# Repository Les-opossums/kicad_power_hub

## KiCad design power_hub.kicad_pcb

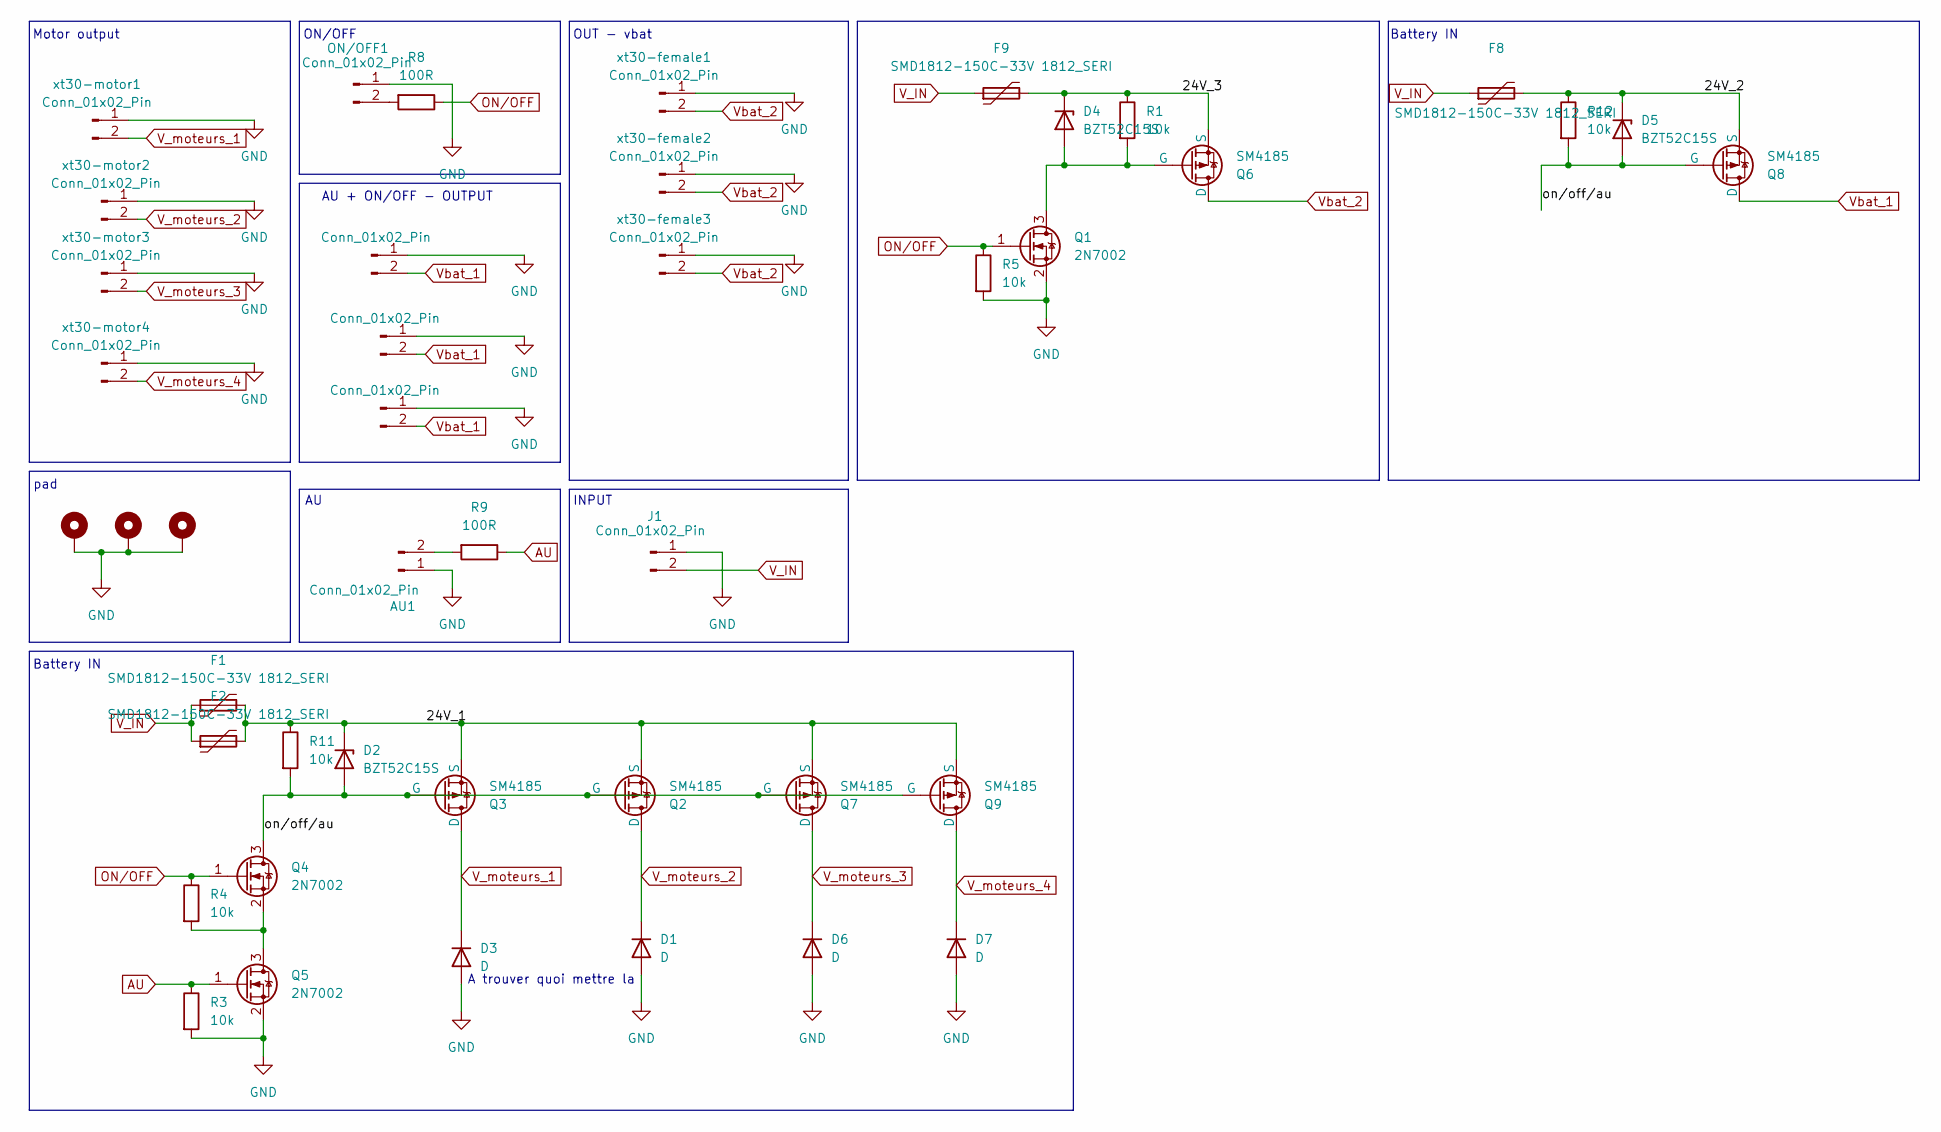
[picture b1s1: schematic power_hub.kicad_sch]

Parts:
AU1: Conn_01x02_Pin; JST_XH_B2B-XH-AM_1x02_P2.50mm_Vertical
D1, D3, D6, D7: D; D_SMA
D2, D4, D5: BZT52C15S; D_SOD-323
F1, F2, F8, F9: SMD1812-150C-33V 1812_SERI; Fuse_Bourns_MF-SM_7.98x5.44mm
H2, H3, H4: MountingHole_Pad; MountingHole_3.2mm_M3_DIN965_Pad
J1: Conn_01x02_Pin; AMASS_XT60-M_1x02_P7.20mm_Vertical
ON/OFF1: Conn_01x02_Pin; JST_XH_B2B-XH-AM_1x02_P2.50mm_Vertical
Q1, Q4, Q5: 2N7002; SOT-23
Q2, Q3, Q6, Q7, Q8, Q9: SM4185; TO-252-2
R1, R3, R4, R5, R11, R12: 10k; R_0805_2012Metric_Pad1.20x1.40mm_HandSolder
R8, R9: 100R; R_0805_2012Metric_Pad1.20x1.40mm_HandSolder
xt30-female1, xt30-female2, xt30-female3, xt30-motor1, xt30-motor2, xt30-motor3, xt30-motor4, xt30-motor5, xt30-motor6, xt30-motor7: Conn_01x02_Pin; AMASS_XT30U-F_1x02_P5.0mm_Vertical

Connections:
/24V_1: D2.1 (K), F1.2, F2.2, Q2.3 (S), Q3.3 (S), Q7.3 (S), Q9.3 (S), R11.1
/24V_2: D5.1 (K), F8.2, Q8.3 (S), R12.1
/24V_3: D4.1 (K), F9.2, Q6.3 (S), R1.1
/on/off/au: D2.2 (A), D5.2 (A), Q2.1 (G), Q3.1 (G), Q4.3 (D), Q7.1 (G), Q8.1 (G), Q9.1 (G), R11.2, R12.2
AU: Q5.1 (G), R3.1, R9.1
GND: AU1.1, D1.2 (A), D3.2 (A), D6.2 (A), D7.2 (A), H2.1, H3.1, H4.1, J1.1, ON/OFF1.1, Q1.2 (S), Q5.2 (S), R3.2, R5.2, xt30-female1.1, xt30-female2.1, xt30-female3.1, xt30-motor1.1, xt30-motor2.1, xt30-motor3.1, xt30-motor4.1, xt30-motor5.1, xt30-motor6.1, xt30-motor7.1
unnamed: AU1.2, R9.2
unnamed: D4.2 (A), Q1.3 (D), Q6.1 (G), R1.2
unnamed: ON/OFF1.2, R8.2
unnamed: Q4.2 (S), Q5.3 (D), R4.2
ON/OFF: Q1.1 (G), Q4.1 (G), R4.1, R5.1, R8.1
V_IN: F1.1, F2.1, F8.1, F9.1, J1.2
V_moteurs_1: D3.1 (K), Q3.2 (D), xt30-motor1.2
V_moteurs_2: D1.1 (K), Q2.2 (D), xt30-motor2.2
V_moteurs_3: D6.1 (K), Q7.2 (D), xt30-motor3.2
V_moteurs_4: D7.1 (K), Q9.2 (D), xt30-motor4.2
Vbat_1: Q8.2 (D), xt30-motor5.2, xt30-motor6.2, xt30-motor7.2
Vbat_2: Q6.2 (D), xt30-female1.2, xt30-female2.2, xt30-female3.2

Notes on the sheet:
AU + ON/OFF - OUTPUT
Motor output
OUT - vbat
Battery IN
INPUT
pad
A trouver quoi mettre la
ON/OFF

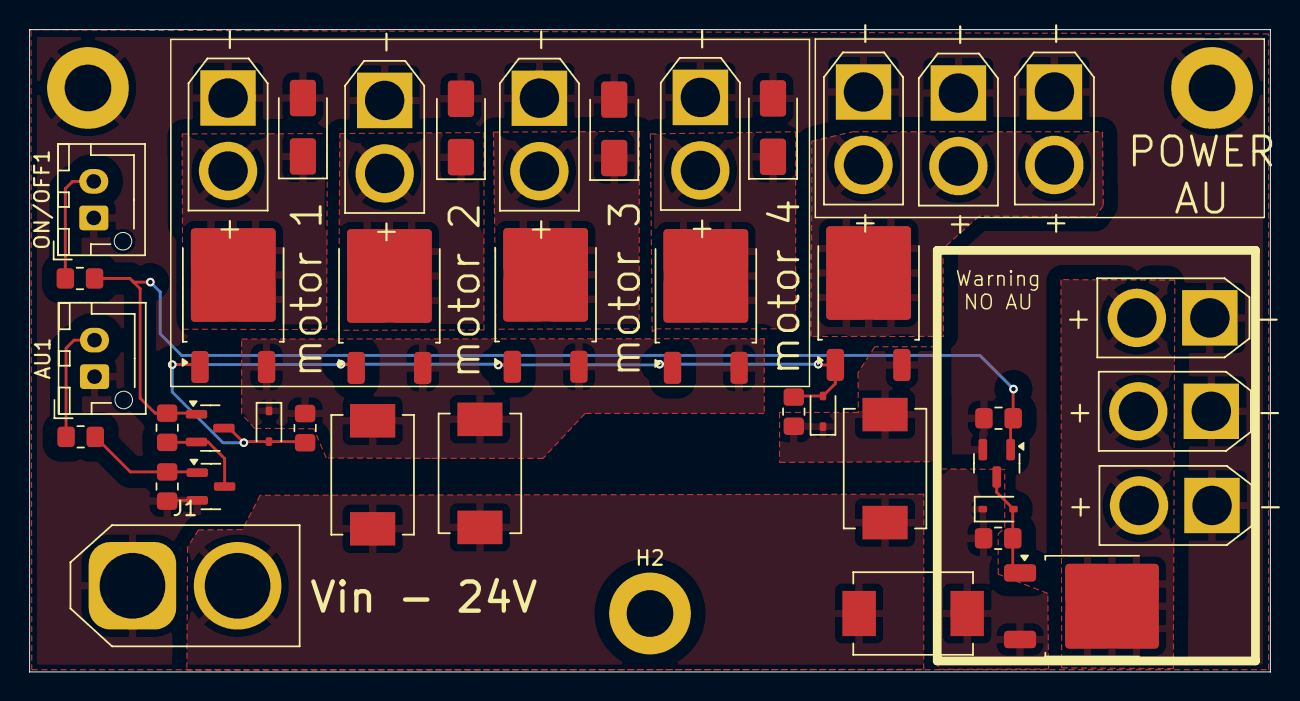
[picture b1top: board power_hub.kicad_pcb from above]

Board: 2 copper layers, 85.0 x 44.0 mm, 44 parts (0 on the bottom side), 18 nets.

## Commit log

2024-08-12 fix issue
2024-08-18 reprise v2
2024-08-19 add schematic
2024-09-09 update schematic and footprint, still a diode to choose
2024-09-11 update step file
2024-12-08 update all
2024-12-23 add serigraphy
2024-12-29 add readme
